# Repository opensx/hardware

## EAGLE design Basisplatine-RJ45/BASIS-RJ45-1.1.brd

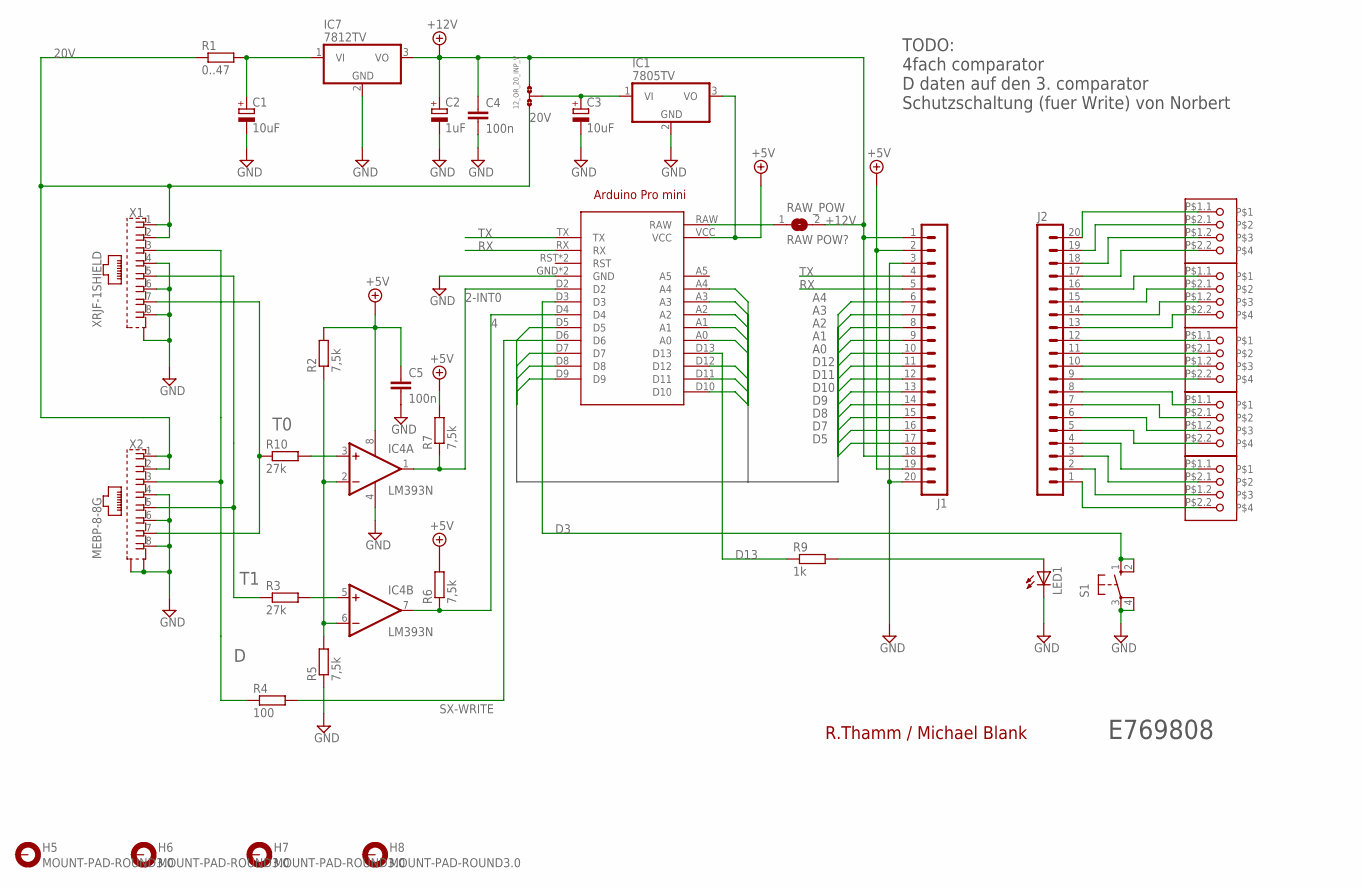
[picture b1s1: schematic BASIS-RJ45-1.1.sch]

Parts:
A5_RX1: 12_OR_20_INP_V; A0R-JMP
ARDUINO2: ARDUINO_PRO_MINI
C1: 10uF; E2,5-7
C2: 1uF; E2,5-7
C3: 10uF; SMC_C
C4, C5: 100n; C050-025X075
H5, H6, H7, H8: MOUNT-PAD-ROUND3.0; 3,0-PAD
IC1: 7805TV; TO220V
IC4: LM393N; DIL08
IC7: 7812TV; TO220V
J1, J2: MA20-1
LED1: LED3MM
R1: 0..47; 0207/12
R2, R5, R6, R7: 7,5k; 0207/10
R3, R10: 27k; 0207/10
R4: 100; 0207/10
R9: 1k; 0207/10
RAW_POW: RAW POW?; SJ
S1: 10-XX; B3F-10XX
U$1, U$2, U$3, U$4, U$5: AKL093-06
X1: XRJF-1SHIELD; XRJF-01A-OHNE_LOCH
X2: MEBP-8-8G; XRJF-01A-0-D2A-010

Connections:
2-INT0: ARDUINO2.D2, IC4.1 (OUT), R7.1
4: ARDUINO2.D4, IC4.7 (OUT), R6.1
20V: A5_RX1.1, R1.1, X1.1, X1.2, X2.1, X2.2
+5V: ARDUINO2.VCC, C5.1, IC1.3 (VO), IC4.8 (V+), J1.2, J1.19, R2.2, R6.2, R7.2
+12V: A5_RX1.3, C2.+, C4.1, IC7.3 (VO), J1.1, J1.18, RAW_POW.2
A0: ARDUINO2.A0, J1.10
A1: ARDUINO2.A1, J1.9
A2: ARDUINO2.A2, J1.8
A3: ARDUINO2.A3, J1.7
A4: ARDUINO2.A4, J1.6
D: R4.1, X1.3, X2.3
D3: ARDUINO2.D3, S1.1 (S), S1.2 (S1)
D5: ARDUINO2.D5, J1.17
D7: ARDUINO2.D7, J1.16
D8: ARDUINO2.D8, J1.15
D9: ARDUINO2.D9, J1.14
D10: ARDUINO2.D10, J1.13
D11: ARDUINO2.D11, J1.12
D12: ARDUINO2.D12, J1.11
D13: ARDUINO2.D13, R9.1
GND: ARDUINO2.GND, ARDUINO2.GND@1 (GND), C1.-, C2.-, C3.-, C4.2, C5.2, IC1.2 (GND), IC4.4 (V-), IC7.2 (GND), J1.3, J1.20, LED1.K (C), R5.1, S1.3, S1.4 (P1), X1.4, X1.6, X1.8, X1.S1 (S), X2.4, X2.6, X2.8, X2.S1 (S), X2.S2 (S)
unnamed: LED1.A, R9.2
unnamed: C1.+, IC7.1 (VI), R1.2
unnamed: IC4.3 (+IN), R10.2
unnamed: IC4.5 (+IN), R3.2
unnamed: J2.1, U$4.P$2.2
unnamed: IC4.2 (-IN), IC4.6 (-IN), R2.1, R5.2
unnamed: J2.2, U$4.P$1.2
unnamed: J2.3, U$4.P$2.1
unnamed: J2.4, U$4.P$1.1
unnamed: J2.5, U$3.P$2.2
unnamed: J2.6, U$3.P$1.2
unnamed: J2.7, U$3.P$2.1
unnamed: J2.8, U$3.P$1.1
unnamed: J2.9, U$1.P$2.2
unnamed: J2.10, U$1.P$1.2
unnamed: J2.11, U$1.P$2.1
unnamed: J2.12, U$1.P$1.1
unnamed: J2.13, U$2.P$2.2
unnamed: J2.14, U$2.P$1.2
unnamed: J2.15, U$2.P$2.1
unnamed: J2.16, U$2.P$1.1
unnamed: J2.17, U$5.P$2.2
unnamed: J2.18, U$5.P$1.2
unnamed: J2.19, U$5.P$2.1
unnamed: J2.20, U$5.P$1.1
unnamed: ARDUINO2.RAW, RAW_POW.1
unnamed: A5_RX1.2, C3.+, IC1.1 (VI)
RX: ARDUINO2.RX, J1.5
SX-WRITE: ARDUINO2.D6, R4.2
T0: R10.1, X1.7, X2.7
T1: R3.1, X1.5, X2.5
TX: ARDUINO2.TX, J1.4

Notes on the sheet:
R.Thamm / Michael Blank
TODO: 4fach comparator D daten auf den 3. comparator Schutzschaltung (fuer Write) von Norbert
E769808

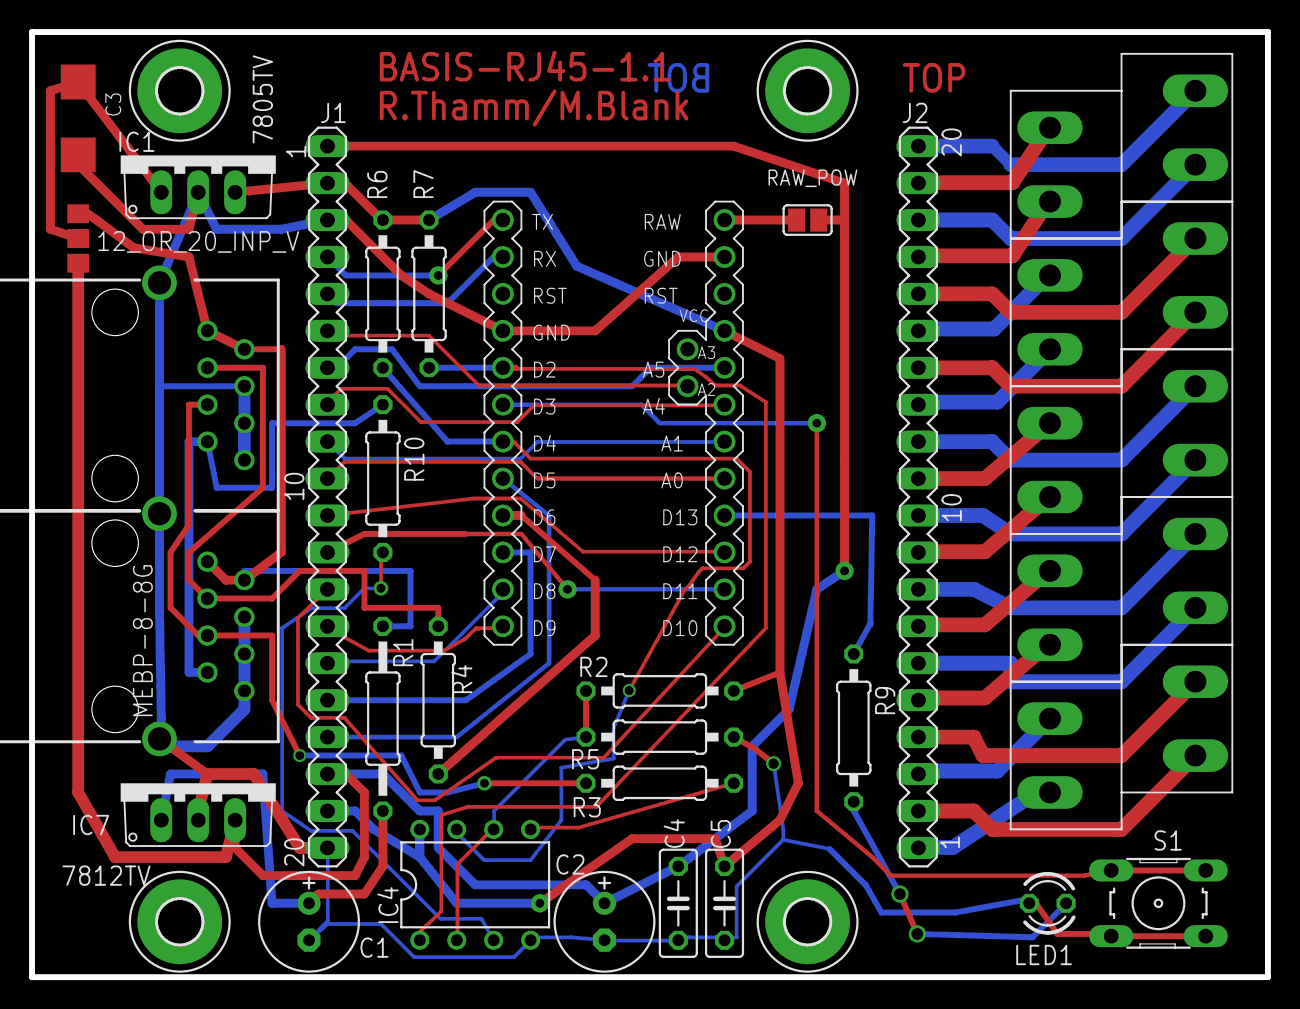
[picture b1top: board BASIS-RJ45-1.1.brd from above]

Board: 2 copper layers, 85.0 x 65.0 mm, 35 parts (0 on the bottom side), 53 nets.

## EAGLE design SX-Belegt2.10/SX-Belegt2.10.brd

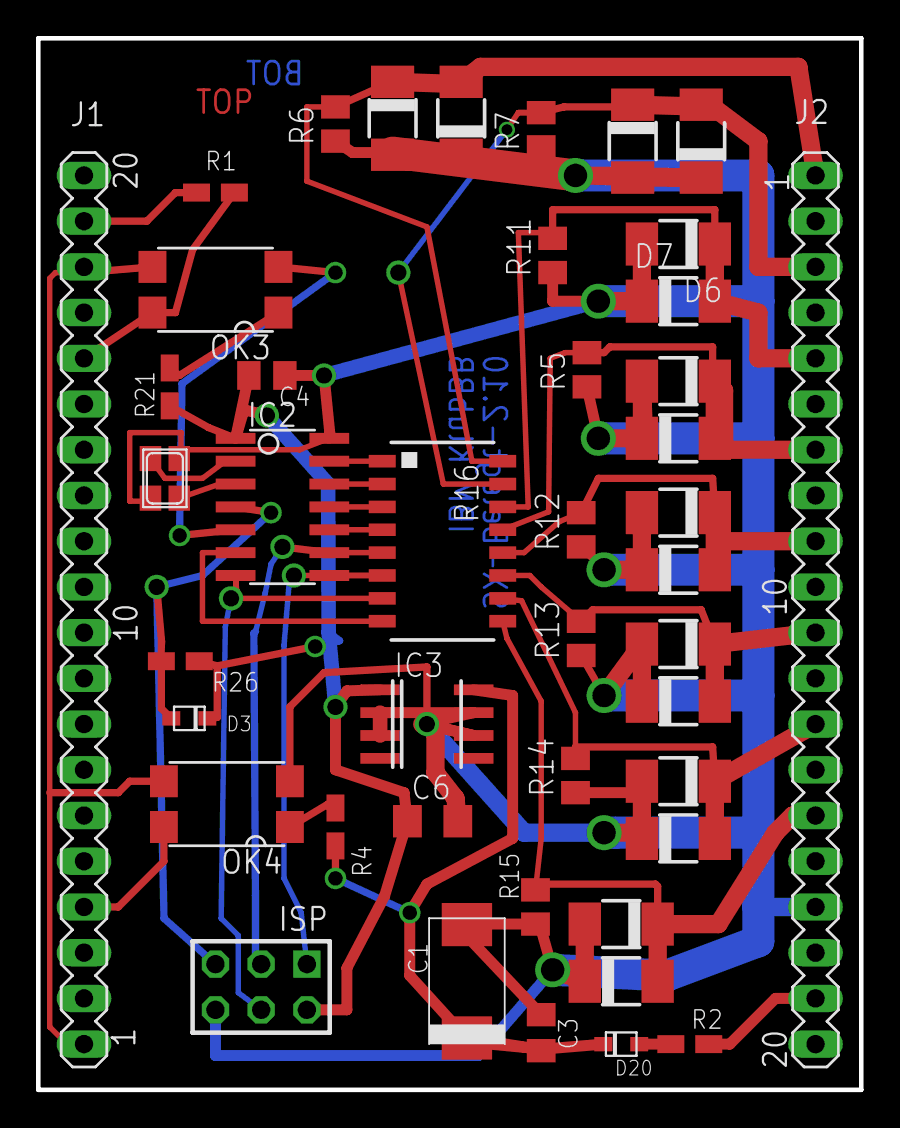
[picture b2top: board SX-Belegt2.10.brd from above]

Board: 2 copper layers, 45.7 x 58.4 mm, 44 parts (0 on the bottom side), 31 nets.

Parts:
C1: 4.7µF; SMC_D
C3, C4: 100n; C0805K
C6: 0.47uF; C1206
D1, D2, D4, D5, D6, D7, D9, D10, D11, D12, D13, D15, D16, D17, D18, D19: SK 34SMA; DO-214AC
D3, D20: 1N4148; SOD-323F
IC2: TINY24/44/84-SSU; SOIC14
IC3: 78L05SMD; SO08
ISP: AVR-ISP-2; AVR-ISP-6
J1, J2: MA20-1
OK3, OK4: LTV357T-SMD; SMD4
Q1: NX3225
R1: 2.2k; R0805W
R2: 200; R0805W
R4, R26: 10k; R0805W
R5, R6, R7, R11, R12, R13, R14, R15: 47; M0805
R16: 4.7k; 4816P
R21: 470; R0805W

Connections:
+5V: C4.1, C6.1, D3.C, IC2.1, IC3.1, ISP.2, R21.2, R26.1
+5V-MAIN: J1.19, R1.1
D5: J1.4, OK4.4
GND: C1.-, C3.2, C4.2, C6.2, D1.A, D2.C, D4.A, D5.C, D6.A, D7.C, D9.A, D10.A, D11.A, D12.A, D13.A, D15.C, D16.C, D17.C, D18.C, D19.C, IC2.14, IC3.2, IC3.3, IC3.6, IC3.7, ISP.6, J2.17, OK4.2, Q1.2, R5.1, R6.1, R7.1, R11.1, R12.1, R13.1, R14.1, R15.1
GND1-MAIN: J1.1, J1.18, OK3.3, OK4.3
MISO: IC2.8, ISP.1, R16.6
MOSI: IC2.7, ISP.4, R16.7
unnamed: IC2.6, R16.8
unnamed: D20.A, R2.2
unnamed: OK4.1, R4.1
unnamed: OK3.1, R21.1
unnamed: IC2.3, Q1.1
unnamed: IC2.2, Q1.3
unnamed: IC2.13, R16.1
unnamed: IC2.5, OK3.2
unnamed: IC2.12, R16.2
unnamed: IC2.10, R16.4
unnamed: IC2.11, R16.3
RST: D3.A, IC2.4, ISP.5, R26.2
RX: J1.16, OK3.4, R1.2
SCK: IC2.9, ISP.3, R16.5
TR1: D13.C, D19.A, J2.15, R15.2, R16.9
TR2: D12.C, D18.A, J2.13, R14.2, R16.10
TR3: D11.C, D17.A, J2.11, R13.2, R16.11
TR4: D10.C, D16.A, J2.9, R12.2, R16.12
TR5: D9.C, D15.A, J2.7, R5.2, R16.13
TR6: D6.C, D7.A, J2.5, R11.2, R16.14
TR7: D4.C, D5.A, J2.3, R7.2, R16.15
TR8: D1.C, D2.A, J2.1, R6.2, R16.16
TR-V: C1.+, C3.1, D20.C, IC3.8, R4.2
TR-V+IN: J2.19, R2.1

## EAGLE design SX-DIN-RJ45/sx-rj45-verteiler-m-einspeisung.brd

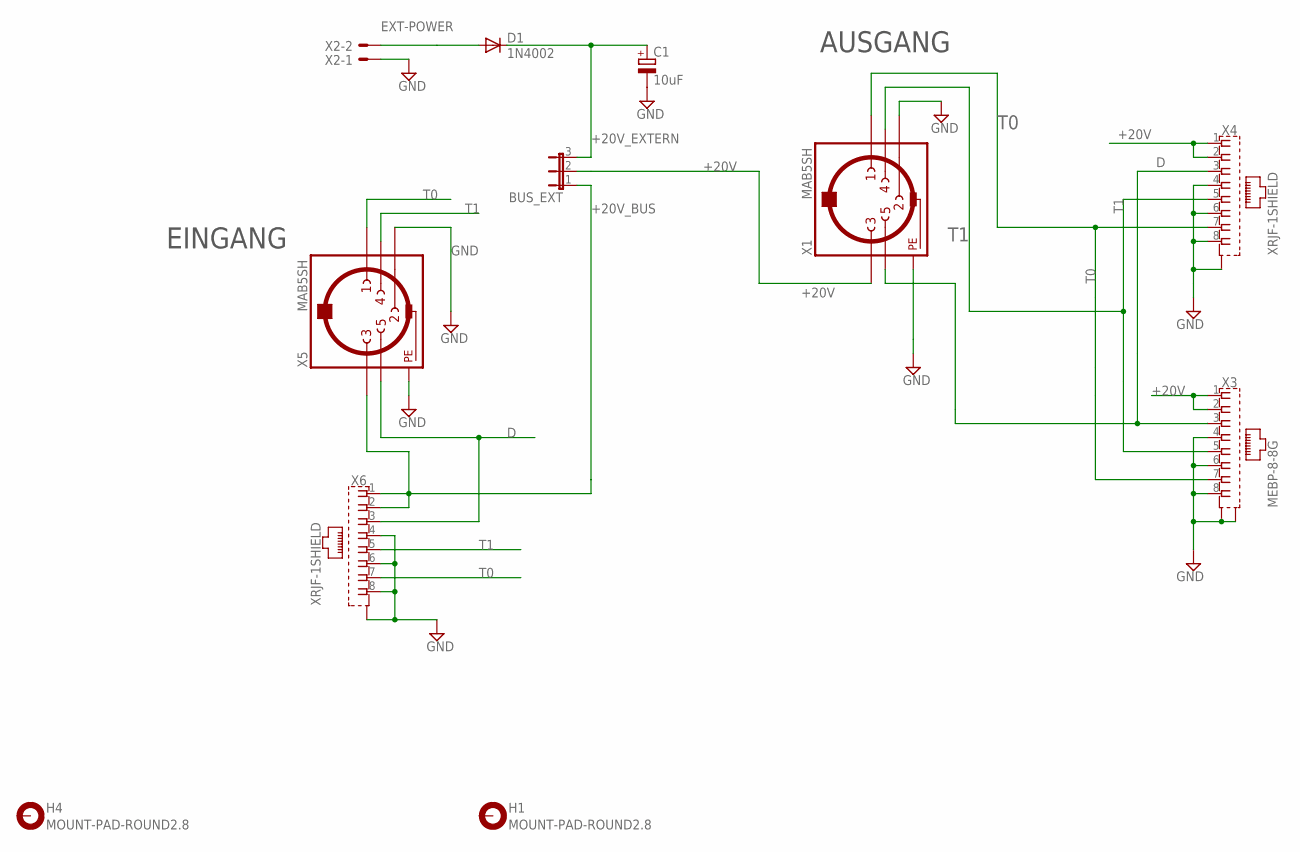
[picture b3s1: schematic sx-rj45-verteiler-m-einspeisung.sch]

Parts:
BUS_EXT: JP2E; JP2
C1: 10uF; E2,5-7
D1: 1N4002; DO201-15
H1, H4: MOUNT-PAD-ROUND2.8; 2,8-PAD
X1, X5: MAB5SH
X2: AKL18X-02W; AKL182-02
X3: MEBP-8-8G; XRJF-01A-0-D2A-010
X4, X6: XRJF-1SHIELD; XRJF-01A-OHNE_LOCH

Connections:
+20V: BUS_EXT.2, X1.3, X3.1, X3.2, X4.1, X4.2
+20V_BUS: BUS_EXT.1, X5.3, X6.1, X6.2
+20V_EXTERN: BUS_EXT.3, C1.+, D1.C
D: X1.5, X3.3, X4.3, X5.5, X6.3
EXT-POWER: D1.A, X2.P$2
GND: C1.-, X1.2, X1.PE, X1.PE1 (PE), X1.PE@ (PE), X1.PE@1 (PE), X2.P$1, X3.4, X3.6, X3.8, X3.S1 (S), X3.S2 (S), X4.4, X4.6, X4.8, X4.S1 (S), X5.2, X5.PE, X5.PE1 (PE), X5.PE@ (PE), X5.PE@1 (PE), X6.4, X6.6, X6.8, X6.S1 (S)
T0: X1.1, X3.7, X4.7, X5.1, X6.7
T1: X1.4, X3.5, X4.5, X5.4, X6.5

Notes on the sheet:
EINGANG
AUSGANG

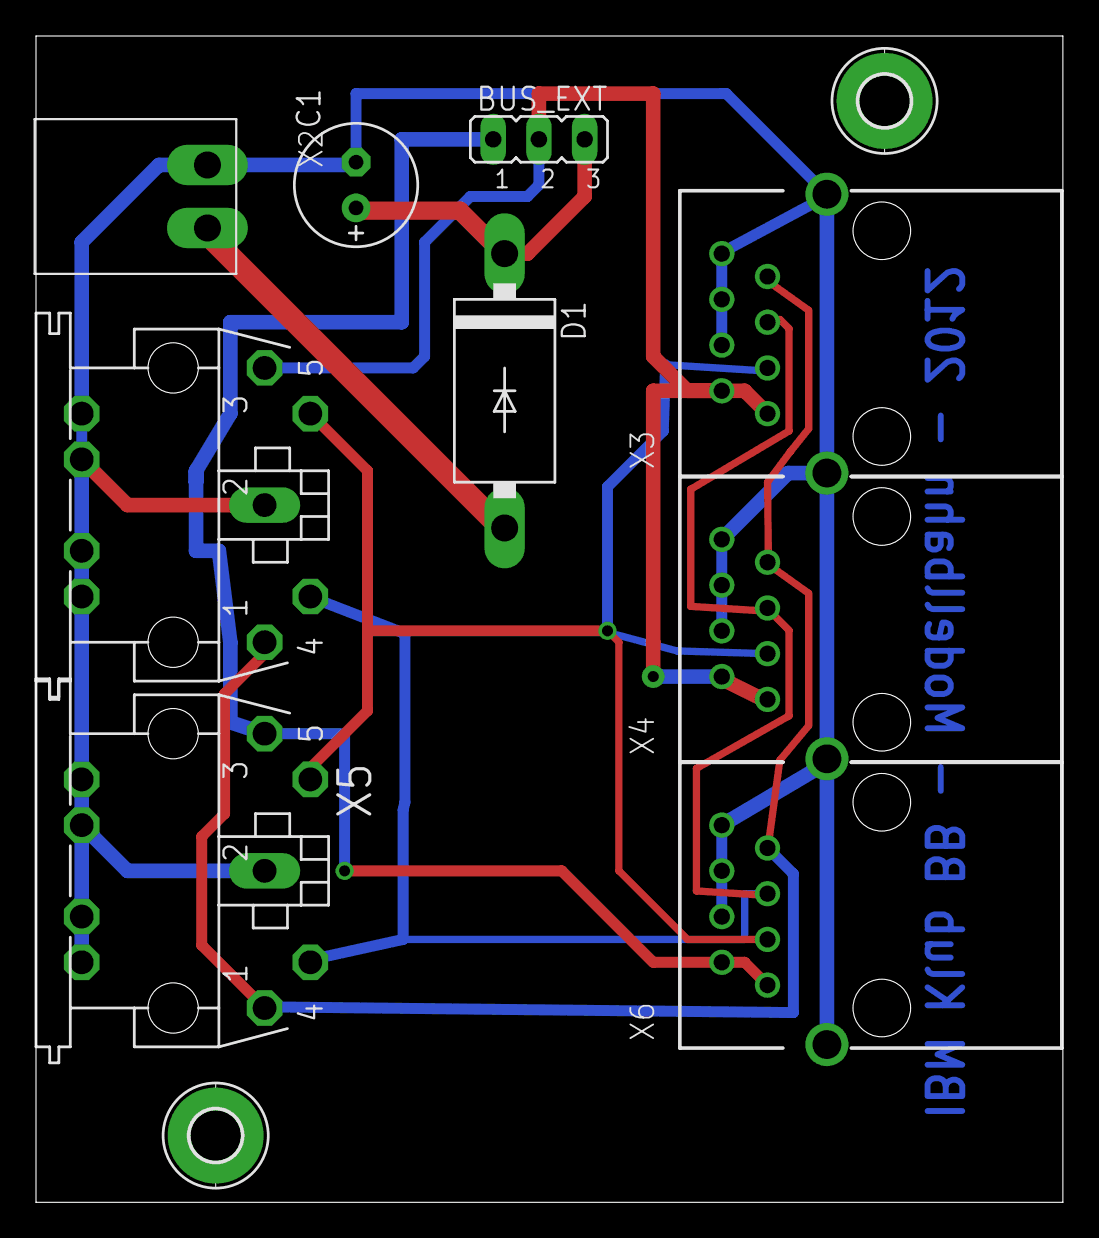
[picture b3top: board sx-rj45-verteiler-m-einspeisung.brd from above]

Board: 2 copper layers, 57.0 x 64.8 mm, 11 parts (0 on the bottom side), 8 nets.
